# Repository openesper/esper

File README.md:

# About Esper

Heavily inspired by the [Pi-Hole](https://github.com/pi-hole/pi-hole), this project aims to bring network wide ad-blocking to another popular device popular among makers and hobbyists, the ESP32.

## What is DNS?

Commonly referred to as the "phone book for the internet", the DNS protocol is how devices map human readable urls like google.com or facebook.com into IP addresses that the device can use.

## How does Esper block ads?

Just like the [Pi-Hole](https://github.com/pi-hole/pi-hole), Esper acts as a DNS server for devices. When sent a DNS query, Esper will read the url the device is requesting, then decide to block the request by returning 0.0.0.0 or forward the request on to a real DNS server.

## Differences between Pi-hole and Esper

The biggest, and most obvious difference is the hardware these projects run on. Pi-hole aims to be available on any Linux powered hardware, while Esper is an ESP32 specific project. Due to being run on a microcontroller, Esper is much more limited in it's capabilities and is therefore much more minimal in it's design.

## Why choose Esper instead of Pi-hole?

Choose whatever one suits you! If you like tinkering with hardware, and do not have much experience with the Raspberry Pi/Linux ecosystem, setting up the Esper software on an ESP32 dev board might be an interesting project. And while Esper may not be nearly as powerful as a Raspberry Pi, DNS protocol is very lightweight in nature. Unless you are in a household with 10+ people that are always online you will likely never going to need more computing power than a microcontroller can provide.

At the same time, if you have no problem using a shell and Linux environment, the Pi-hole is a much more feature rich and powerful piece of software that is a joy to use.

## How can I get an Esper?

The easiest way, is to purchase a pre-made one from the [Tindie store](https://www.tindie.com/products/esper/esper/).

If you have some ESP32 development boards collecting dust, it will work on those too! ([Just follow the instructions here!](https://github.com/openesper/esper/blob/main/software/README.md))

DISCLAIMER: It is **heavily** recommended to use a device with ethernet. Even the best Wifi will significantly increase latency and decrease reliability compared to a good copper connection.

If you want to try you hand an making an Esper from scratch, the repository contains all the schematic, pcb, and enclosure files needed to build one yourself.

## Reprogramming Esper

Do you like the Esper hardware, but want to use it for something other than ad-blocking? Great! The Esper hardware is completely reprogrammable and includes an on-board USB-UART converter, no extra programmers are needed!

# Esper Development

## Tools Used

* KiCAD	- EDA tool used to design PCB
* FreeCAD - 3D modeling tool for designing enclosure
* ESP-IDF - Contains ESP32 API and build tools for firmware development
* Python 3.7 - Scripts to glue everything together

## Directory Structure

    ├── hardware                    # Hardware root directory
    │   ├── custom components           # Custom KiCad component files
    │   ├── enclosure                   # FreeCAD project and STL files for enclosure
    │   ├── product                     # KiCad projects for Esper
    │   │   ├── usb-programmable        	# Includes CP2102 for easy usb programming
    │   │   └── jtag-header             	# 10-pin header for JTAG & UART, meant to be used with programmer
    │   └── programmer                  # KiCad project for programmer/debugger
    └── software                    # Software root directory
        ├── firmware                    # ESP-IDF project that contains all code for Esper
        ├── scripts                     # Scripts used in build process and testing
        └── website                     # For website development, contains symbolic links to HTML files

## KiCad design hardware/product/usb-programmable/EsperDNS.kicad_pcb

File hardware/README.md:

# Esper Hardware Design

## Goals

All Esper hardware is designed to be as easy to modify and manufacture as possible. For the most part this means using free, open-source tools and simplifying the design to have the smallest DOM possible. 

### PCB & Schematic

KiCAD is used for all PCB design since it is free and has a large community support. 

### Manufacturing

The Esper device is designed to be manufactured and assembled at JLCPCB. At low quantities (5-10 boards), no other board house comes close on price and ease of use.

This may change in the future if other companies start matching JLCPCB in price, or if Esper starts being manufactures at higher volumes.

### Part Selection

To make the process of manufacturing and assembly as easy as possible, all components (except connectors) are chosen from the [JLCPCB parts library](https://jlcpcb.com/parts) so JLCPCB assembly service can be used. This means that connectors are the only parts that need to be hand soldered, but JLC recently added connectors to their parts library so this may change soon.

Also, in order to minimize the amount of work needed to keep custom schematic symbols and footprints up-to-date, it was a priority to minimize the amount of custom components and only use parts found in the default KiCAD library. Almost every part in the project has footprints and symbols included in KiCAD, or has an equivalent component included.

### Enclosure

There are many 3D modeling tools out there, to varying degrees of free-ness, but I am not qualified to go over the pros and cons of each. FreeCAD was chosen for this project simply because it seemed to be the most popular open-source program, but almost any would work.

The enclosure is currently designed to be 3D printed, but alternatives are being looked into.

## BOM

To fully assemble an Esper, these parts are needed:

| Part | Quantity |
| --- | --- |
| Enclosure Top | 1 |
| Enclosure Bottom | 1 |
| Enclosure Dome | 1 |
| Esper PCBA | 1 |
| [Heat-Set Inserts (M2 x 0.4mm) x 2.5mm](https://www.mcmaster.com/catalog/127/3973) | 2 |
| [Screws (M2 x 0.4mm) x 6mm](https://www.mcmaster.com/catalog/127/3251) | 2 |

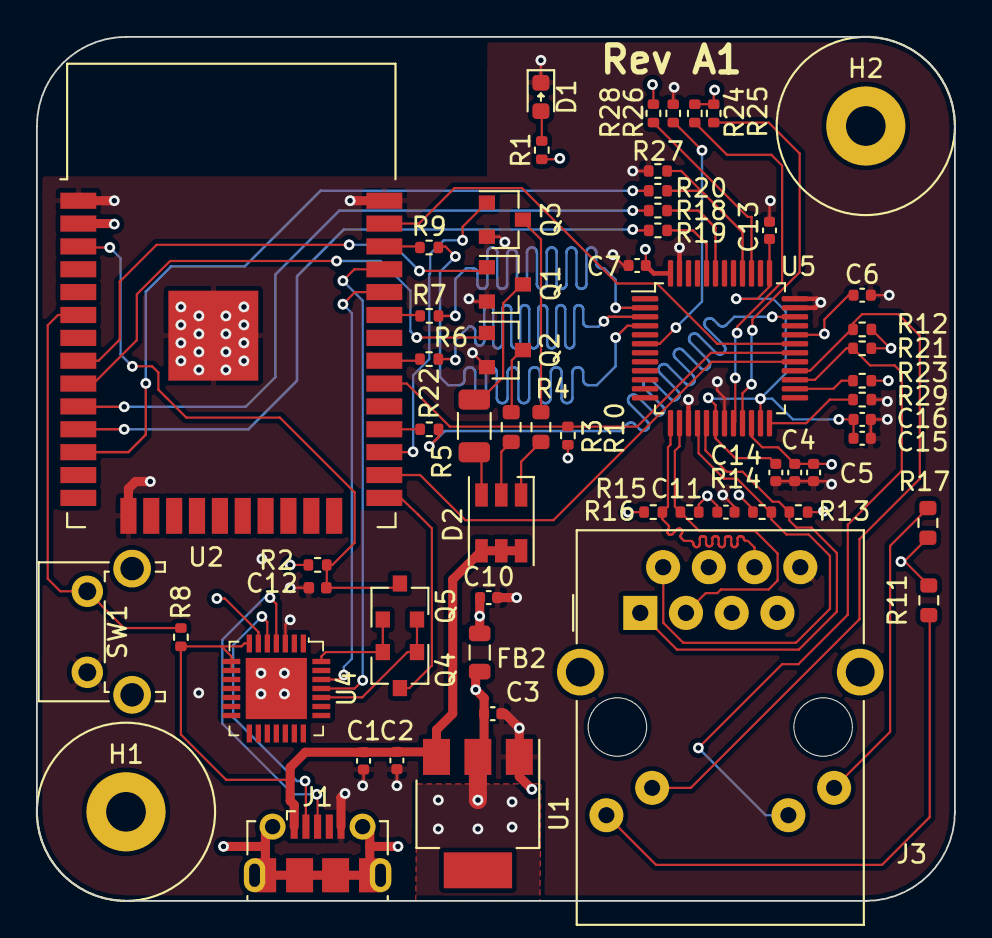
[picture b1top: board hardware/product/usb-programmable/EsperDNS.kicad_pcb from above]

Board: 4 copper layers, 51.0 x 48.0 mm, 60 parts (0 on the bottom side), 56 nets.

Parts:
C1, C4, C12: 1uF; C_0402_1005Metric
C2, C5, C6, C7, C11, C13, C14, C16: 0.1uF; C_0402_1005Metric
C3, C10, C15: 10uF; C_0402_1005Metric
D1: GRN; D_0603_1608Metric
D2: RS-3535MWAR; LED_RGB_PLCC-6
FB2: Ferrite_Bead; L_0805_2012Metric
H1, H2: MountingHole; MountingHole_2.2mm_M2_Pad
J1: USB_B_Micro; USB_Micro-B_Molex-105017-0001
J3: RJ45_Amphenol_RJMG1BD3B8K1ANR
Q1, Q2, Q3, Q4, Q5: 2N7002; SOT-23
R1: 470; R_0402_1005Metric
R2, R8: 10K; R_0402_1005Metric
R3, R4: 47; R_0603_1608Metric
R5: 82; R_1206_3216Metric
R6, R7, R9, R13, R14, R15, R16, R18, R19, R20, R22: 49.9; R_0402_1005Metric
R10, R12, R21, R23, R24, R25, R26, R27, R28: 2.2k; R_0402_1005Metric
R11, R17: 270; R_0603_1608Metric
R29: 4.87; R_0402_1005Metric
SW1: PTS645VH83-2 LFS; SW_Tactile_SPST_Angled_PTS645Vx83-2LFS
U1: AZ1117EH-3.3TRG1; SOT-223
U2: ESP32-WROOM-32E; ESP32-WROOM-32
U4: CP2102-GMR_NRND; VFQFN-28-1EP_5x5mm
U5: DP83848C; LQFP-48_7x7mm_P0.5mm

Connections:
+3.3VA: C4.1, C5.1, C10.1, C11.1, FB2.1, J3.R4, J3.R5, R11.1, R13.1, R14.1, R15.1, R16.1, R17.1, U5.22
+3V3: C3.1, C6.1, C7.1, FB2.2, R1.1, R2.2, R10.1, R12.1, R21.1, R23.1, R24.1, R25.1, R26.1, U1.2, U2.2, U4.6, U5.32, U5.48
/CLK_R: R22.2, U2.28
/CRS_DV_R: R20.1, R27.1, U5.40
/D+: J1.3, U4.4
/D-: J1.2, U4.5
/LEDG_A: J3.L4, R11.2
/LEDY_A: J3.L1, R17.2
/LED_ACT: R23.2, U5.26
/LED_LINK: J3.L3, R12.2, U5.28
/LED_SPEED: J3.L2, R21.2, U5.27
/MII_MODE: R26.2, U5.39
/PFB: C13.1, C14.1, C15.1, C16.1, U5.18, U5.23, U5.37
/RBIAS: R29.1, U5.24
/RD+: J3.R3, R15.2, U5.14
/RD-: J3.R6, R16.2, U5.13
/RESERVED0: R24.2, U5.20
/RESERVED1: R25.2, U5.21
/RX0_R: R18.1, U5.43
/RX1_R: R19.1, U5.44
/SNI_MODE: R28.1, U5.6
/TD+: J3.R1, R13.2, U5.17
/TD-: J3.R2, R14.2, U5.16
/TXD0_R: R6.1, U2.31
/TXD1_R: R9.1, U2.36
/TXEN_R: R7.1, U2.33
Block: R8.2, SW1.2, U2.6
Blue: Q3.1, U2.27
CLK_RMII: R22.1, U5.34
CRS_DV: R20.2, U2.12
DTR: Q4.2, Q5.1, U4.28
EN: C12.1, Q5.3, R2.1, U2.3
Earth: H1.1, H2.1, J1.6, J3.13
GND: C1.2, C2.2, C3.2, C4.2, C5.2, C6.2, C7.2, C10.2, C11.2, C12.2, C13.2, C14.2, C15.2, C16.2, D1.1, J1.5, J3.R8, Q1.2, Q2.2, Q3.2, R27.2, R28.2, R29.2, SW1.1, U1.1, U2.1, U2.15, U2.38, U2.39, U4.3, U4.29, U5.15, U5.19, U5.35, U5.36, U5.47
Green: Q2.1, U2.9
IO0: Q4.3, U2.25
MDC: U2.37, U5.31
MDIO: R10.2, U2.30, U5.30
unnamed: D1.2, R1.2
unnamed: D2.1, R3.1
unnamed: D2.2, R4.1
unnamed: D2.3, R5.1
unnamed: Q1.3, R5.2
unnamed: Q2.3, R4.2
unnamed: Q3.3, R3.2
RTS: Q4.1, Q5.2, U4.24
RX: U2.35, U4.25
RXD0: R18.2, U2.10
RXD1: R19.2, U2.11
Red: Q1.1, U2.8
TX: U2.34, U4.26
TXD0: R6.2, U5.3
TXD1: R9.2, U5.4
TXEN: R7.2, U5.2
VBUS: C1.1, C2.1, D2.4, D2.5, D2.6, J1.1, R8.1, U1.3, U4.7, U4.8, U4.9
nRST: U2.26, U5.29

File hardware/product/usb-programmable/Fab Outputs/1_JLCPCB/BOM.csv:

Comment,Designator,Footprint,LCSC
"1uF","C1,C4,C12","Capacitor_SMD:C_0402_1005Metric","C52923"
"10uF","C3,C10,C15","Capacitor_SMD:C_0402_1005Metric","C15525"
"0.1uF","C2,C5,C6,C7,C11,C13,C14,C16","Capacitor_SMD:C_0402_1005Metric","C1525"
"GRN","D1","Diode_SMD:D_0603_1608Metric","C72043"
"RS-3535MWAR","D2","LED_SMD:LED_RGB_PLCC-6"," C110402"
"Ferrite_Bead","FB2","Inductor_SMD:L_0805_2012Metric","C1015"
"MountingHole","H1,H2","MountingHole:MountingHole_2.2mm_M2_Pad",""
"USB_B_Micro","J1","Connector_USB:USB_Micro-B_Molex-105017-0001",""
"RJ45_Amphenol_RJMG1BD3B8K1ANR","J3","Connector_RJ:RJ45_Amphenol_RJMG1BD3B8K1ANR",""
"2N7002","Q1,Q2,Q3,Q4,Q5","Package_TO_SOT_SMD:SOT-23","C8545"
"470","R1","Resistor_SMD:R_0402_1005Metric"," C25117"
"2.2k","R10,R12,R21,R23,R24,R25,R26,R27,R28","Resistor_SMD:R_0402_1005Metric","C25879"
"270","R11,R17","Resistor_SMD:R_0603_1608Metric","C22966"
"10K","R2,R8","Resistor_SMD:R_0402_1005Metric","C25744"
"4.87","R29","Resistor_SMD:R_0402_1005Metric","C25902"
"47","R3,R4","Resistor_SMD:R_0603_1608Metric","C23182"
"82","R5","Resistor_SMD:R_1206_3216Metric","C247183"
"49.9","R6,R7,R9,R13,R14,R15,R16,R18,R19,R20,R22","Resistor_SMD:R_0402_1005Metric","C25120"
"PTS645VH83-2 LFS","SW1","Button_Switch_THT:SW_Tactile_SPST_Angled_PTS645Vx83-2LFS",""
"AZ1117EH-3.3TRG1","U1","Package_TO_SOT_SMD:SOT-223","C108494"
"ESP32-WROOM-32E","U2","RF_Module:ESP32-WROOM-32","C701341"
"CP2102-GMR_NRND","U4","EsperFootprints:VFQFN-28-1EP_5x5mm"," C6568"
"DP83848C","U5","Package_QFP:LQFP-48_7x7mm_P0.5mm","C16688"

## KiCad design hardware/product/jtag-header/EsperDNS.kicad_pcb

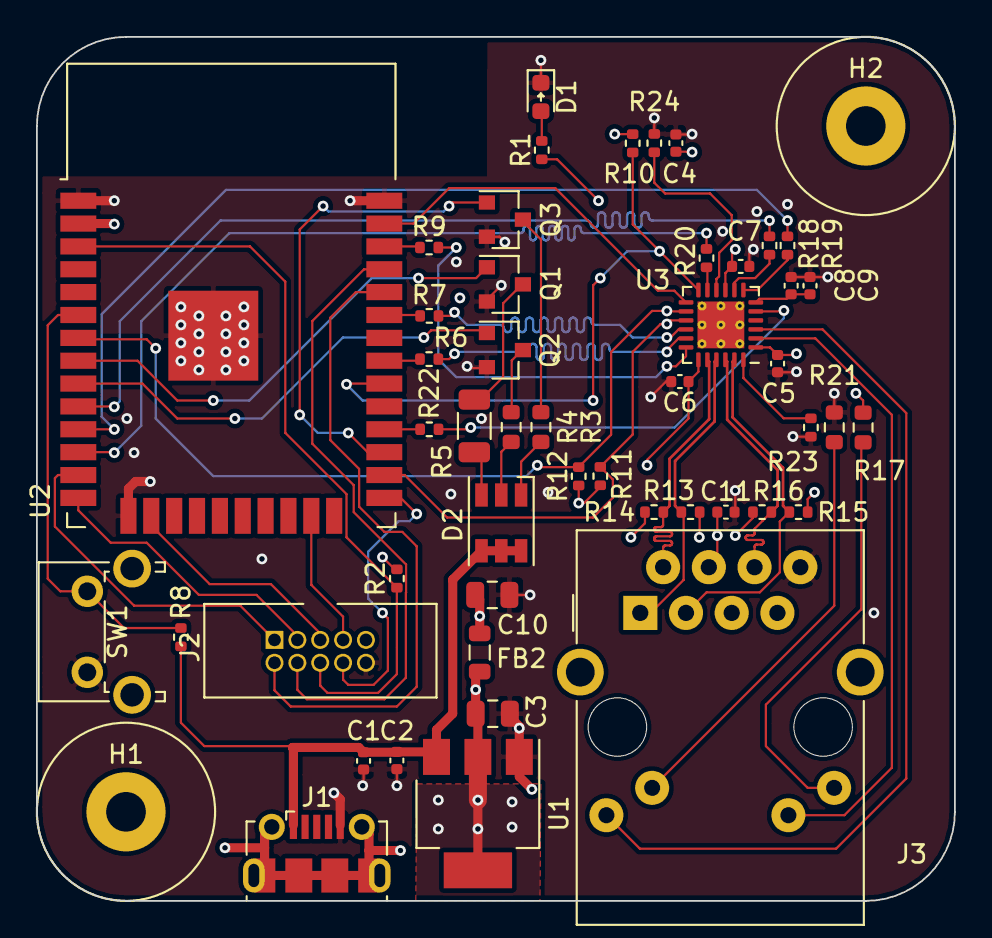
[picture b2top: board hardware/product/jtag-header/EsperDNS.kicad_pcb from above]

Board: 4 copper layers, 51.0 x 48.0 mm, 50 parts (0 on the bottom side), 53 nets.

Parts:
C1, C4, C9: 1uF; C_0402_1005Metric
C2, C5, C6, C7, C8, C11: 0.1uF; C_0402_1005Metric
C3, C10: 10uF; C_0805_2012Metric
D1: GRN; D_0603_1608Metric
D2: RS-3535MWAR; LED_RGB_PLCC-6
FB2: Ferrite_Bead; L_0805_2012Metric
H1, H2: MountingHole; MountingHole_2.2mm_M2_Pad
J1: USB_B_Micro; USB_Micro-B_Molex-105017-0001
J2: Conn_02x05_Odd_Even; CNC_3220-10-0100-00
J3: RJ45_Amphenol_RJMG1BD3B8K1ANR
Q1, Q2, Q3: 2N7002; SOT-23
R1: 470; R_0402_1005Metric
R2, R8, R10, R11, R12, R24: 10K; R_0402_1005Metric
R3, R4: 47; R_0603_1608Metric
R5: 82; R_1206_3216Metric
R6, R7, R9, R13, R14, R15, R16, R18, R19, R20, R22: 49.9; R_0402_1005Metric
R17, R21: 270; R_0603_1608Metric
R23: 12.1K; R_0402_1005Metric
SW1: PTS645VH83-2 LFS; SW_Tactile_SPST_Angled_PTS645Vx83-2LFS
U1: AZ1117EH-3.3TRG1; SOT-223
U2: ESP32-WROOM-32E; ESP32-WROOM-32
U3: LAN8720A; QFN-24-1EP_4x4mm_P0.5mm_EP2.6x2.6mm_ThermalVias

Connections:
+3.3VA: C4.1, C5.1, C6.1, C10.1, C11.1, FB2.1, J3.R4, J3.R5, R10.1, R11.1, R12.1, R13.1, R14.1, R15.1, R16.1, R17.1, U3.1, U3.19
+3V3: C3.1, C7.1, FB2.2, R1.1, R2.2, U1.2, U2.2, U3.9
/CLK_R: R22.2, U2.28
/CRS_DV_R: R20.1, U3.11
/LEDG_K: J3.L3, R21.1
/LEDY_A: J3.L1, R17.2
/PHYAD0: R24.1, U3.10
/RBIAS: R23.1, U3.24
/RD+: J3.R3, R15.2, U3.23
/RD-: J3.R6, R16.2, U3.22
/RX0_R: R18.1, U3.8
/RX1_R: R19.1, U3.7
/TD+: J3.R1, R13.2, U3.21
/TD-: J3.R2, R14.2, U3.20
/TXD0_R: R6.1, U2.31
/TXD1_R: R9.1, U2.36
/TXEN_R: R7.1, U2.33
Block: R8.2, SW1.2, U2.6
Blue: Q3.1, U2.27
CLK50MHZ: R22.1, U3.5
CRS_DV: R20.2, U2.12
EN: J2.6, R2.1, U2.3
Earth: H1.1, H2.1, J1.6, J3.13
GND: C1.2, C2.2, C3.2, C4.2, C5.2, C6.2, C7.2, C8.2, C9.2, C10.2, C11.2, D1.1, J1.5, J2.10, J3.R8, Q1.2, Q2.2, Q3.2, R21.2, R23.2, R24.2, SW1.1, U1.1, U2.1, U2.15, U2.38, U2.39, U3.25
Green: Q2.1, U2.9
IO0: J2.8, U2.25
LED1_REGOFF: J3.L4, U3.3
LED2_nINTSEL: J3.L2, U3.2
MDC: U2.37, U3.13
MDIO: R10.2, U2.30, U3.12
MTCK: J2.5, U2.16
MTDI: J2.3, U2.14
MTDO: J2.7, U2.23
MTMS: J2.1, U2.13
unnamed: D1.2, R1.2
unnamed: D2.1, R3.1
unnamed: D2.2, R4.1
unnamed: D2.3, R5.1
unnamed: Q1.3, R5.2
unnamed: Q2.3, R4.2
unnamed: Q3.3, R3.2
RX: J2.4, U2.35
RXD0: R18.2, U2.10
RXD1: R19.2, U2.11
Red: Q1.1, U2.8
TX: J2.2, U2.34
TXD0: R6.2, U3.17
TXD1: R9.2, U3.18
TXEN: R7.2, U3.16
VBUS: C1.1, C2.1, D2.4, D2.5, D2.6, J1.1, R8.1, U1.3
VDDCR: C8.1, C9.1, U3.6
nINT: R12.2, U2.7, U3.14
nRST: R11.2, U2.26, U3.15

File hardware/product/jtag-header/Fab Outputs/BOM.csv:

Comment,Designator,Footprint,LCSC
"1uF","C1,C4,C9","Capacitor_SMD:C_0402_1005Metric","C52923"
"10uF","C3,C10","Capacitor_SMD:C_0805_2012Metric","C15850"
"0.1uF","C2,C5,C6,C7,C8,C11","Capacitor_SMD:C_0402_1005Metric","C1525"
"GRN","D1","Diode_SMD:D_0603_1608Metric","C72043"
"RS-3535MWAR","D2","LED_SMD:LED_RGB_PLCC-6"," C110402"
"Ferrite_Bead","FB2","Inductor_SMD:L_0805_2012Metric","C1015"
"MountingHole","H1,H2","MountingHole:MountingHole_2.2mm_M2_Pad",""
"USB_B_Micro","J1","Connector_USB:USB_Micro-B_Molex-105017-0001",""
"Conn_02x05_Odd_Even","J2","EsperFootprints:CNC_3220-10-0100-00",""
"RJ45_Amphenol_RJMG1BD3B8K1ANR","J3","Connector_RJ:RJ45_Amphenol_RJMG1BD3B8K1ANR",""
"2N7002","Q1,Q2,Q3","Package_TO_SOT_SMD:SOT-23","C8545"
"470","R1","Resistor_SMD:R_0402_1005Metric"," C25117"
"10K","R2,R8,R10,R11,R12,R24","Resistor_SMD:R_0402_1005Metric","C25744"
"270","R17,R21","Resistor_SMD:R_0603_1608Metric","C22966"
"12.1K","R23","Resistor_SMD:R_0402_1005Metric","C25852"
"47","R3,R4","Resistor_SMD:R_0603_1608Metric","C23182"
"82","R5","Resistor_SMD:R_1206_3216Metric","C247183"
"49.9","R6,R7,R9,R13,R14,R15,R16,R18,R19,R20,R22","Resistor_SMD:R_0402_1005Metric","C25120"
"PTS645VH83-2 LFS","SW1","Button_Switch_THT:SW_Tactile_SPST_Angled_PTS645Vx83-2LFS",""
"AZ1117EH-3.3TRG1","U1","Package_TO_SOT_SMD:SOT-223","C108494"
"ESP32-WROOM-32E","U2","RF_Module:ESP32-WROOM-32","C701341"
"LAN8720A","U3","Package_DFN_QFN:QFN-24-1EP_4x4mm_P0.5mm_EP2.6x2.6mm_ThermalVias","C45223"

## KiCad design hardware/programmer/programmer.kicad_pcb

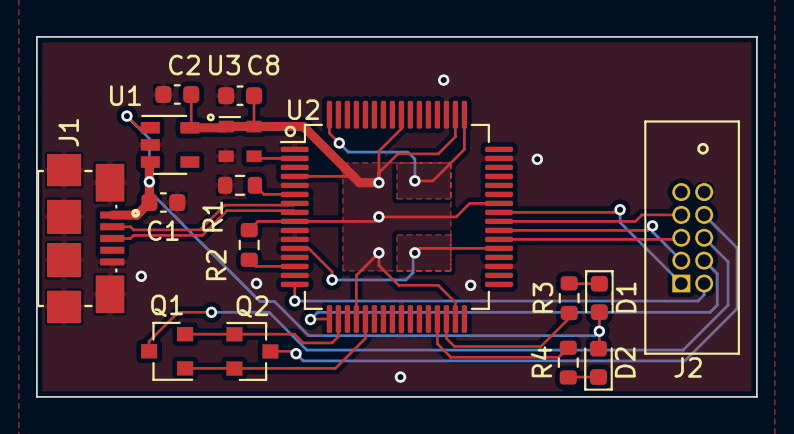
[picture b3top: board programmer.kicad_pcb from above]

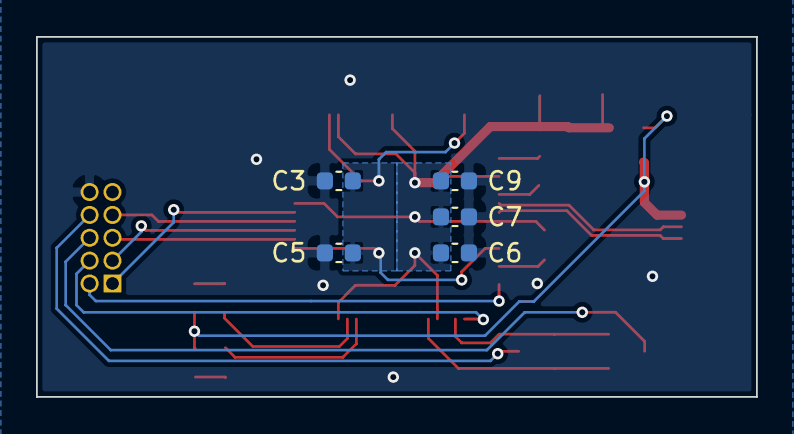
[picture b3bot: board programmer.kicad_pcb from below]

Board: 2 copper layers, 40.0 x 20.0 mm, 21 parts (5 on the bottom side), 23 nets.

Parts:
C1, C2, C5, C6, C7, C8, C9: 0.1uF; C_0603_1608Metric
C3: 1uF; C_0603_1608Metric
D1: BLU; LED_0603_1608Metric
D2: GRN; LED_0603_1608Metric
J1: 10118192-0001LF; AMPHENOL_10118192-0001LF
J2: 3220-10-0100-00; CNC_3220-10-0100-00
Q1, Q2: 2N7002ET1G; SOT-23
R1, R2: 12K; R_0603_1608Metric
R3, R4: 470; R_0603_1608Metric
U1: TLV75533PDBV; SOT-23-5
U2: FT2232HL; LQFP-64_10x10mm_P0.5mm
U3: ASDMB-12.000MHz; Oscillator_SMD_Abracon_ASDMB-4Pin_2.5x2.0mm

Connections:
+1V8: C3.1, C5.1, U2.12, U2.37, U2.49, U2.64
+3V3: C2.1, C6.1, C7.1, C8.1, C9.1, R2.2, U1.5, U2.4, U2.9, U2.20, U2.31, U2.42, U2.50, U2.56, U3.1, U3.4
/OSCI: U2.2, U3.3
/REF: R1.1, U2.6
/RESET: R2.1, U2.14
D+: J1.3, U2.8
D-: J1.2, U2.7
DTR#: Q1.1, Q2.2, U2.21
EN: J2.6, Q1.3
GND: C1.2, C2.2, C3.2, C5.2, C6.2, C7.2, C8.2, C9.2, J1.5, J1.6, J2.10, R1.2, U1.2, U2.1, U2.5, U2.10, U2.11, U2.13, U2.15, U2.25, U2.35, U2.47, U2.51, U3.2
IO0: J2.8, Q2.3
unnamed: D1.1, R3.1
unnamed: D2.1, R4.1
RTS#: Q1.2, Q2.1, U2.18
RX: J2.4, U2.17
RXLED#: R4.2, U2.29
TCK: J2.5, U2.38
TDI: J2.3, U2.39
TDO: J2.7, U2.40
TMS: J2.1, U2.41
TX: J2.2, U2.16
TXLED#: R3.2, U2.30
VBUS: C1.1, D1.2, D2.2, J1.1, U1.1, U1.3

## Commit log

2021-04-11 Bugfixes for bugs found in first set of tests
    Bugsfixes:
    - Changed sdkconfig.defaults to use version in CMakeLists.txt
    - Added a provisioned flag in flash, fixing problem of Esper
    incorrectly thinking it was finished during provisioning
    - Added gpio_enabled checks in gpio.c so no errors would be
    thrown if gpio was disabled
2021-04-12 Added LED blink when query is blocked
    Bugfixes:
    - Fixed bug in detecting restart after OTA
    - Corrected string formating (%*s to %.*s)
2021-04-15 Fixed "Restarting" popup bug
    In some cases, the "Restarting..." popup after OTA would not
    go away, this commit fixes that.
    Other
    - Updates to ToDo.md
    - Changed OTA config to use just hostname, instead of whole path
    - Changed sdkconfig.defaults to reflect OTA change
2021-04-16 Fixed bug in OTA rollback
    Logic for pushbutton timing was wrong, so device would
    never rollback no matter how long button is held
2021-04-16 Updated Version number to 00.00.03
2021-04-22 Testing having blacklist in spiffs
2021-04-23 Still testing new webserver design
2021-04-23 Implements /spiffs/ota_0 and /spiffs/ota_1
2021-04-23 Working on wifi configuration
2021-04-25 Reworked provisioning mostly working
    also added a test server in website directory
2021-04-27 Finished provisioning server, added NVS checks
2021-04-28 Added blacklist add/remove, and changed to LittleFS
2021-04-29 Now in cpp
2021-04-29 Added settings component, more progress on settings page
2021-04-30 Added settings & toggleblock POST handlers
2021-04-30 Working on OTA
2021-05-03 Changed settings/ota/filesystem to use exceptions & namespaces
2021-05-03 Adding some try/catch
2021-05-03 Updating DNS component to c++
2021-05-04 Packet parsing working
2021-05-04 More progress on DNS
2021-05-05 DNS working so far, no ip6 support
2021-05-06 DNS tested and working, with logging
2021-05-07 Reformatted component directories, added debug component
2021-05-07 Changed to new PHY
2021-05-15 GPIO code now working
2021-05-15 Completed testing
2021-05-15 Updated README and MANUAL
2021-05-16 Even more changes to documentation
2021-05-16 Updated defaultblacklist.txt and console logging
2021-05-16 Updated manual
